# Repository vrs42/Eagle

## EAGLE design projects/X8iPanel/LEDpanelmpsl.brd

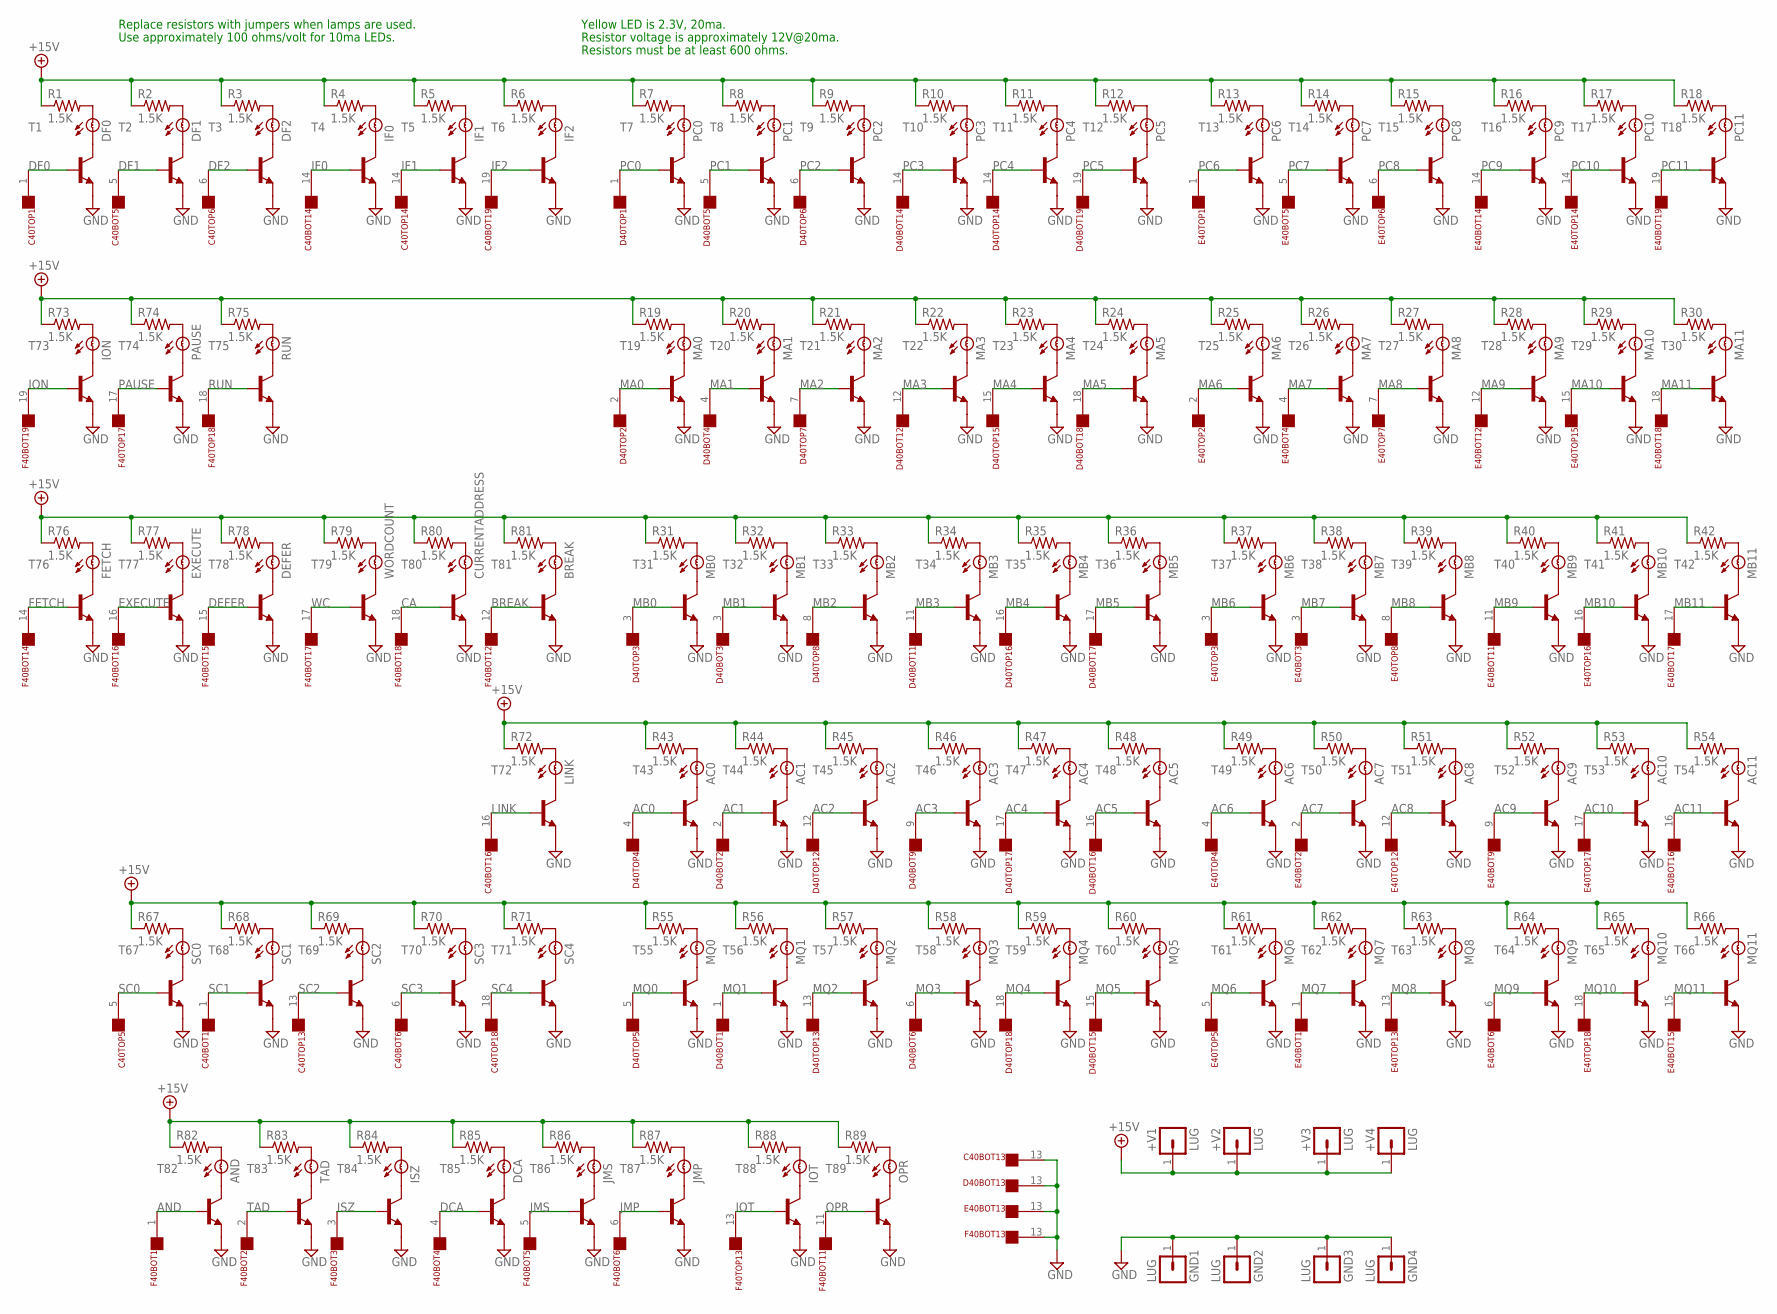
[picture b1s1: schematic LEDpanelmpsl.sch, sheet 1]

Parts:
+V1, +V2, +V3, +V4: LUG; SPADELUG
AC0, AC1, AC2, AC3, AC4, AC5, AC6, AC7, AC8, AC9, AC10, AC11: BULB
AND: BULB
BREAK: BULB
C40BOT, C40TOP: FLEX19
CURRENTADDRESS: BULB
D40BOT, D40TOP: FLEX19
DCA: BULB
DEFER: BULB
DF0, DF1, DF2: BULB
E40BOT, E40TOP: FLEX19
EXECUTE: BULB
F40BOT, F40TOP: FLEX19
FETCH: BULB
GND1, GND2, GND3, GND4: LUG; SPADELUG
IF0, IF1, IF2: BULB
ION: BULB
IOT: BULB
ISZ: BULB
JMP: BULB
JMS: BULB
LINK: BULB
MA0, MA1, MA2, MA3, MA4, MA5, MA6, MA7, MA8, MA9, MA10, MA11: BULB
MB0, MB1, MB2, MB3, MB4, MB5, MB6, MB7, MB8, MB9, MB10, MB11: BULB
MQ0, MQ1, MQ2, MQ3, MQ4, MQ5, MQ6, MQ7, MQ8, MQ9, MQ10, MQ11: BULB
OPR: BULB
PAUSE: BULB
PC0, PC1, PC2, PC3, PC4, PC5, PC6, PC7, PC8, PC9, PC10, PC11: BULB
R1, R2, R3, R4, R5, R6, R7, R8, R9, R10, R11, R12, R13, R14, R15, R16, R17, R18, R19, R20, R21, R22, R23, R24, R25, R26, R27, R28, R29, R30, R31, R32, R33, R34, R35, R36, R37, R38, R39, R40, R41, R42, R43, R44, R45, R46, R47, R48, R49, R50, R51, R52, R53, R54, R55, R56, R57, R58, R59, R60, R61, R62, R63, R64, R65, R66, R67, R68, R69, R70, R71, R72, R73, R74, R75, R76, R77, R78, R79, R80, R81, R82, R83, R84, R85, R86, R87, R88, R89: 1.5K; 0207/10
RUN: BULB
SC0, SC1, SC2, SC3, SC4: BULB
T1, T2, T3, T4, T5, T6, T7, T8, T9, T10, T11, T12, T13, T14, T15, T16, T17, T18, T19, T20, T21, T22, T23, T24, T25, T26, T27, T28, T29, T30, T31, T32, T33, T34, T35, T36, T37, T38, T39, T40, T41, T42, T43, T44, T45, T46, T47, T48, T49, T50, T51, T52, T53, T54, T55, T56, T57, T58, T59, T60, T61, T62, T63, T64, T65, T66, T67, T68, T69, T70, T71, T72, T73, T74, T75, T76, T77, T78, T79, T80, T81, T82, T83, T84, T85, T86, T87, T88, T89: MPS2222A-NPN-TO92-CBE; TO92-CBE
TAD: BULB
WORDCOUNT: BULB

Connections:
+15V: +V1.1, +V2.1, +V3.1, +V4.1, R1.1, R2.1, R3.1, R4.1, R5.1, R6.1, R7.1, R8.1, R9.1, R10.1, R11.1, R12.1, R13.1, R14.1, R15.1, R16.1, R17.1, R18.1, R19.1, R20.1, R21.1, R22.1, R23.1, R24.1, R25.1, R26.1, R27.1, R28.1, R29.1, R30.1, R31.1, R32.1, R33.1, R34.1, R35.1, R36.1, R37.1, R38.1, R39.1, R40.1, R41.1, R42.1, R43.1, R44.1, R45.1, R46.1, R47.1, R48.1, R49.1, R50.1, R51.1, R52.1, R53.1, R54.1, R55.1, R56.1, R57.1, R58.1, R59.1, R60.1, R61.1, R62.1, R63.1, R64.1, R65.1, R66.1, R67.1, R68.1, R69.1, R70.1, R71.1, R72.1, R73.1, R74.1, R75.1, R76.1, R77.1, R78.1, R79.1, R80.1, R81.1, R82.1, R83.1, R84.1, R85.1, R86.1, R87.1, R88.1, R89.1
AC0: D40TOP.4, T43.B; also elsewhere on the board
AC1: D40BOT.2, T44.B; also elsewhere on the board
AC2: D40TOP.12, T45.B; also elsewhere on the board
AC3: D40BOT.9, T46.B; also elsewhere on the board
AC4: D40TOP.17, T47.B; also elsewhere on the board
AC5: D40BOT.16, T48.B; also elsewhere on the board
AC6: E40TOP.4, T49.B; also elsewhere on the board
AC7: E40BOT.2, T50.B; also elsewhere on the board
AC8: E40TOP.12, T51.B; also elsewhere on the board
AC9: E40BOT.9, T52.B; also elsewhere on the board
AC10: E40TOP.17, T53.B; also elsewhere on the board
AC11: E40BOT.16, T54.B; also elsewhere on the board
AND: F40BOT.1, T82.B; also elsewhere on the board
BREAK: F40BOT.12, T81.B; also elsewhere on the board
CA: F40BOT.18, T80.B; also elsewhere on the board
DCA: F40BOT.4, T85.B; also elsewhere on the board
DEFER: F40BOT.15, T78.B; also elsewhere on the board
DF0: C40TOP.1, T1.B; also elsewhere on the board
DF1: C40BOT.5, T2.B; also elsewhere on the board
DF2: C40TOP.6, T3.B; also elsewhere on the board
EXECUTE: F40BOT.16, T77.B; also elsewhere on the board
FETCH: F40BOT.14, T76.B; also elsewhere on the board
GND: C40BOT.13, D40BOT.13, E40BOT.13, F40BOT.13, GND1.1, GND2.1, GND3.1, GND4.1, T1.E, T2.E, T3.E, T4.E, T5.E, T6.E, T7.E, T8.E, T9.E, T10.E, T11.E, T12.E, T13.E, T14.E, T15.E, T16.E, T17.E, T18.E, T19.E, T20.E, T21.E, T22.E, T23.E, T24.E, T25.E, T26.E, T27.E, T28.E, T29.E, T30.E, T31.E, T32.E, T33.E, T34.E, T35.E, T36.E, T37.E, T38.E, T39.E, T40.E, T41.E, T42.E, T43.E, T44.E, T45.E, T46.E, T47.E, T48.E, T49.E, T50.E, T51.E, T52.E, T53.E, T54.E, T55.E, T56.E, T57.E, T58.E, T59.E, T60.E, T61.E, T62.E, T63.E, T64.E, T65.E, T66.E, T67.E, T68.E, T69.E, T70.E, T71.E, T72.E, T73.E, T74.E, T75.E, T76.E, T77.E, T78.E, T79.E, T80.E, T81.E, T82.E, T83.E, T84.E, T85.E, T86.E, T87.E, T88.E, T89.E; also elsewhere on the board
IF0: C40BOT.14, T4.B; also elsewhere on the board
IF1: C40TOP.14, T5.B; also elsewhere on the board
IF2: C40BOT.19, T6.B; also elsewhere on the board
ION: F40BOT.19, T73.B; also elsewhere on the board
IOT: F40TOP.13, T88.B; also elsewhere on the board
ISZ: F40BOT.3, T84.B; also elsewhere on the board
JMP: F40BOT.6, T87.B; also elsewhere on the board
JMS: F40BOT.5, T86.B; also elsewhere on the board
LINK: C40BOT.16, T72.B; also elsewhere on the board
MA0: D40TOP.2, T19.B; also elsewhere on the board
MA1: D40BOT.4, T20.B; also elsewhere on the board
MA2: D40TOP.7, T21.B; also elsewhere on the board
MA3: D40BOT.12, T22.B; also elsewhere on the board
MA4: D40TOP.15, T23.B; also elsewhere on the board
MA5: D40BOT.18, T24.B; also elsewhere on the board
MA6: E40TOP.2, T25.B; also elsewhere on the board
MA7: E40BOT.4, T26.B; also elsewhere on the board
MA8: E40TOP.7, T27.B; also elsewhere on the board
MA9: E40BOT.12, T28.B; also elsewhere on the board
MA10: E40TOP.15, T29.B; also elsewhere on the board
MA11: E40BOT.18, T30.B; also elsewhere on the board
MB0: D40TOP.3, T31.B; also elsewhere on the board
MB1: D40BOT.3, T32.B; also elsewhere on the board
MB2: D40TOP.8, T33.B; also elsewhere on the board
MB3: D40BOT.11, T34.B; also elsewhere on the board
MB4: D40TOP.16, T35.B; also elsewhere on the board
MB5: D40BOT.17, T36.B; also elsewhere on the board
MB6: E40TOP.3, T37.B; also elsewhere on the board
MB7: E40BOT.3, T38.B; also elsewhere on the board
MB8: E40TOP.8, T39.B; also elsewhere on the board
MB9: E40BOT.11, T40.B; also elsewhere on the board
MB10: E40TOP.16, T41.B; also elsewhere on the board
MB11: E40BOT.17, T42.B; also elsewhere on the board
MQ0: D40TOP.5, T55.B; also elsewhere on the board
MQ1: D40BOT.1, T56.B; also elsewhere on the board
MQ2: D40TOP.13, T57.B; also elsewhere on the board
MQ3: D40BOT.6, T58.B; also elsewhere on the board
MQ4: D40TOP.18, T59.B; also elsewhere on the board
MQ5: D40BOT.15, T60.B; also elsewhere on the board
MQ6: E40TOP.5, T61.B; also elsewhere on the board
MQ7: E40BOT.1, T62.B; also elsewhere on the board
MQ8: E40TOP.13, T63.B; also elsewhere on the board
MQ9: E40BOT.6, T64.B; also elsewhere on the board
MQ10: E40TOP.18, T65.B; also elsewhere on the board
MQ11: E40BOT.15, T66.B; also elsewhere on the board
unnamed: DF0.B, T1.C
unnamed: DF1.B, T2.C
unnamed: DF2.B, T3.C
unnamed: IF0.B, T4.C
unnamed: IF1.B, T5.C
unnamed: IF2.B, T6.C
unnamed: PC0.B, T7.C
unnamed: PC1.B, T8.C
unnamed: PC2.B, T9.C
unnamed: PC3.B, T10.C
unnamed: PC4.B, T11.C
unnamed: PC5.B, T12.C
unnamed: PC6.B, T13.C
unnamed: PC7.B, T14.C
unnamed: PC8.B, T15.C
unnamed: PC9.B, T16.C
unnamed: PC10.B, T17.C
unnamed: PC11.B, T18.C
unnamed: MA0.B, T19.C
unnamed: MA1.B, T20.C
unnamed: MA2.B, T21.C
unnamed: MA3.B, T22.C
unnamed: MA4.B, T23.C
unnamed: MA5.B, T24.C
unnamed: MA6.B, T25.C
unnamed: MA7.B, T26.C
unnamed: MA8.B, T27.C
unnamed: MA9.B, T28.C
unnamed: MA10.B, T29.C
unnamed: MA11.B, T30.C
unnamed: MB0.B, T31.C
unnamed: MB1.B, T32.C
unnamed: MB2.B, T33.C
unnamed: MB3.B, T34.C
unnamed: MB4.B, T35.C
unnamed: MB5.B, T36.C
unnamed: MB6.B, T37.C
unnamed: MB7.B, T38.C
unnamed: MB8.B, T39.C
unnamed: MB9.B, T40.C
unnamed: MB10.B, T41.C
unnamed: MB11.B, T42.C
unnamed: AC0.B, T43.C
unnamed: AC1.B, T44.C
unnamed: AC2.B, T45.C
unnamed: AC3.B, T46.C
unnamed: AC4.B, T47.C
unnamed: AC5.B, T48.C
unnamed: AC6.B, T49.C
unnamed: AC7.B, T50.C
unnamed: AC8.B, T51.C
unnamed: AC9.B, T52.C
unnamed: AC10.B, T53.C
unnamed: AC11.B, T54.C
unnamed: MQ0.B, T55.C
unnamed: MQ1.B, T56.C
unnamed: MQ2.B, T57.C
unnamed: MQ3.B, T58.C
unnamed: MQ4.B, T59.C
unnamed: MQ5.B, T60.C
unnamed: MQ6.B, T61.C
unnamed: MQ7.B, T62.C
unnamed: MQ8.B, T63.C
unnamed: MQ9.B, T64.C
unnamed: MQ10.B, T65.C
unnamed: MQ11.B, T66.C
unnamed: SC0.B, T67.C
unnamed: SC1.B, T68.C
unnamed: SC2.B, T69.C
unnamed: SC3.B, T70.C
unnamed: SC4.B, T71.C
unnamed: LINK.B, T72.C
unnamed: ION.B, T73.C
unnamed: PAUSE.B, T74.C
unnamed: RUN.B, T75.C
unnamed: FETCH.B, T76.C
unnamed: EXECUTE.B, T77.C
unnamed: DEFER.B, T78.C
unnamed: T79.C, WORDCOUNT.B
unnamed: CURRENTADDRESS.B, T80.C
unnamed: BREAK.B, T81.C
unnamed: AND.B, T82.C
unnamed: T83.C, TAD.B
unnamed: ISZ.B, T84.C
unnamed: DCA.B, T85.C
unnamed: JMS.B, T86.C
unnamed: JMP.B, T87.C
unnamed: IOT.B, T88.C
unnamed: OPR.B, T89.C
unnamed: DF0.A, R1.2
unnamed: DF1.A, R2.2
unnamed: DF2.A, R3.2
unnamed: IF0.A, R4.2
unnamed: IF1.A, R5.2
unnamed: IF2.A, R6.2
unnamed: PC0.A, R7.2
unnamed: PC1.A, R8.2
unnamed: PC2.A, R9.2
unnamed: PC3.A, R10.2
unnamed: PC4.A, R11.2
unnamed: PC5.A, R12.2
unnamed: PC6.A, R13.2
unnamed: PC7.A, R14.2
unnamed: PC8.A, R15.2
unnamed: PC9.A, R16.2
unnamed: PC10.A, R17.2
unnamed: PC11.A, R18.2
unnamed: ION.A, R73.2
unnamed: PAUSE.A, R74.2
unnamed: R75.2, RUN.A
unnamed: MA0.A, R19.2
unnamed: MA1.A, R20.2
unnamed: MA2.A, R21.2
unnamed: MA3.A, R22.2
unnamed: MA4.A, R23.2
unnamed: MA5.A, R24.2
unnamed: MA6.A, R25.2
unnamed: MA7.A, R26.2
unnamed: MA8.A, R27.2
unnamed: MA9.A, R28.2
unnamed: MA10.A, R29.2
unnamed: MA11.A, R30.2
unnamed: FETCH.A, R76.2
unnamed: EXECUTE.A, R77.2
unnamed: DEFER.A, R78.2
unnamed: R79.2, WORDCOUNT.A
unnamed: CURRENTADDRESS.A, R80.2
unnamed: BREAK.A, R81.2
unnamed: LINK.A, R72.2
unnamed: MB0.A, R31.2
unnamed: MB1.A, R32.2
unnamed: MB2.A, R33.2
unnamed: MB3.A, R34.2
unnamed: MB4.A, R35.2
unnamed: MB5.A, R36.2
unnamed: MB6.A, R37.2
unnamed: MB7.A, R38.2
unnamed: MB8.A, R39.2
unnamed: MB9.A, R40.2
unnamed: MB10.A, R41.2
unnamed: MB11.A, R42.2
unnamed: AC0.A, R43.2
unnamed: AC1.A, R44.2
unnamed: AC2.A, R45.2
unnamed: AC3.A, R46.2
unnamed: AC4.A, R47.2
unnamed: AC5.A, R48.2
unnamed: AC6.A, R49.2
unnamed: AC7.A, R50.2
unnamed: AC8.A, R51.2
unnamed: AC9.A, R52.2
unnamed: AC10.A, R53.2
unnamed: AC11.A, R54.2
unnamed: R67.2, SC0.A
unnamed: R68.2, SC1.A
unnamed: R69.2, SC2.A
unnamed: R70.2, SC3.A
unnamed: R71.2, SC4.A
unnamed: MQ11.A, R66.2
unnamed: MQ10.A, R65.2
unnamed: MQ9.A, R64.2
unnamed: MQ8.A, R63.2
unnamed: MQ7.A, R62.2
unnamed: MQ6.A, R61.2
unnamed: MQ5.A, R60.2
unnamed: MQ4.A, R59.2
unnamed: MQ3.A, R58.2
unnamed: MQ2.A, R57.2
unnamed: MQ1.A, R56.2
unnamed: MQ0.A, R55.2
unnamed: AND.A, R82.2
unnamed: R83.2, TAD.A
unnamed: ISZ.A, R84.2
unnamed: DCA.A, R85.2
unnamed: JMS.A, R86.2
unnamed: JMP.A, R87.2
unnamed: IOT.A, R88.2
unnamed: OPR.A, R89.2
OPR: F40BOT.11, T89.B; also elsewhere on the board
PAUSE: F40TOP.17, T74.B; also elsewhere on the board
PC0: D40TOP.1, T7.B; also elsewhere on the board
PC1: D40BOT.5, T8.B; also elsewhere on the board
PC2: D40TOP.6, T9.B; also elsewhere on the board
PC3: D40BOT.14, T10.B; also elsewhere on the board
PC4: D40TOP.14, T11.B; also elsewhere on the board
PC5: D40BOT.19, T12.B; also elsewhere on the board
PC6: E40TOP.1, T13.B; also elsewhere on the board
PC7: E40BOT.5, T14.B; also elsewhere on the board
PC8: E40TOP.6, T15.B; also elsewhere on the board
PC9: E40BOT.14, T16.B; also elsewhere on the board
PC10: E40TOP.14, T17.B; also elsewhere on the board
PC11: E40BOT.19, T18.B; also elsewhere on the board
RUN: F40TOP.18, T75.B; also elsewhere on the board
SC0: C40TOP.5, T67.B; also elsewhere on the board
SC1: C40BOT.1, T68.B; also elsewhere on the board
SC2: C40TOP.13, T69.B; also elsewhere on the board
SC3: C40BOT.6, T70.B; also elsewhere on the board
SC4: C40TOP.18, T71.B; also elsewhere on the board
TAD: F40BOT.2, T83.B; also elsewhere on the board
WC: F40BOT.17, T79.B; also elsewhere on the board

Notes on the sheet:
Replace resistors with jumpers when lamps are used.
Use approximately 100 ohms/volt for 10ma LEDs.
Yellow LED is 2.3V, 20ma.
Resistor voltage is approximately 12V@20ma.
Resistors must be at least 600 ohms.

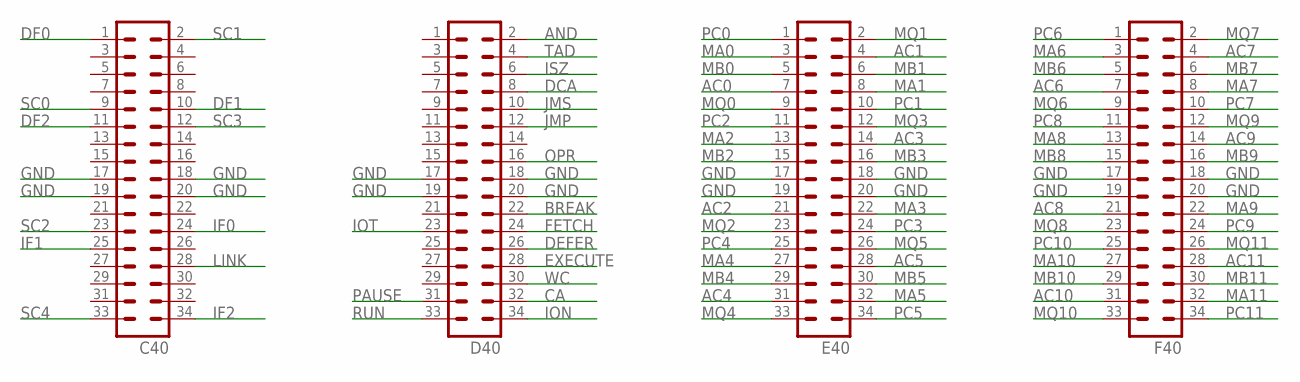
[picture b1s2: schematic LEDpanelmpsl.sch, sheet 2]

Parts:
C40: MA17-2
D40: MA17-2
E40: MA17-2
F40: MA17-2

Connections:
AC0: E40.7; also elsewhere on the board
AC1: E40.4; also elsewhere on the board
AC2: E40.21; also elsewhere on the board
AC3: E40.14; also elsewhere on the board
AC4: E40.31; also elsewhere on the board
AC5: E40.28; also elsewhere on the board
AC6: F40.7; also elsewhere on the board
AC7: F40.4; also elsewhere on the board
AC8: F40.21; also elsewhere on the board
AC9: F40.14; also elsewhere on the board
AC10: F40.31; also elsewhere on the board
AC11: F40.28; also elsewhere on the board
AND: D40.2; also elsewhere on the board
BREAK: D40.22; also elsewhere on the board
CA: D40.32; also elsewhere on the board
DCA: D40.8; also elsewhere on the board
DEFER: D40.26; also elsewhere on the board
DF0: C40.1; also elsewhere on the board
DF1: C40.10; also elsewhere on the board
DF2: C40.11; also elsewhere on the board
EXECUTE: D40.28; also elsewhere on the board
FETCH: D40.24; also elsewhere on the board
GND: C40.17, C40.18, C40.19, C40.20, D40.17, D40.18, D40.19, D40.20, E40.17, E40.18, E40.19, E40.20, F40.17, F40.18, F40.19, F40.20; also elsewhere on the board
IF0: C40.24; also elsewhere on the board
IF1: C40.25; also elsewhere on the board
IF2: C40.34; also elsewhere on the board
ION: D40.34; also elsewhere on the board
IOT: D40.23; also elsewhere on the board
ISZ: D40.6; also elsewhere on the board
JMP: D40.12; also elsewhere on the board
JMS: D40.10; also elsewhere on the board
LINK: C40.28; also elsewhere on the board
MA0: E40.3; also elsewhere on the board
MA1: E40.8; also elsewhere on the board
MA2: E40.13; also elsewhere on the board
MA3: E40.22; also elsewhere on the board
MA4: E40.27; also elsewhere on the board
MA5: E40.32; also elsewhere on the board
MA6: F40.3; also elsewhere on the board
MA7: F40.8; also elsewhere on the board
MA8: F40.13; also elsewhere on the board
MA9: F40.22; also elsewhere on the board
MA10: F40.27; also elsewhere on the board
MA11: F40.32; also elsewhere on the board
MB0: E40.5; also elsewhere on the board
MB1: E40.6; also elsewhere on the board
MB2: E40.15; also elsewhere on the board
MB3: E40.16; also elsewhere on the board
MB4: E40.29; also elsewhere on the board
MB5: E40.30; also elsewhere on the board
MB6: F40.5; also elsewhere on the board
MB7: F40.6; also elsewhere on the board
MB8: F40.15; also elsewhere on the board
MB9: F40.16; also elsewhere on the board
MB10: F40.29; also elsewhere on the board
MB11: F40.30; also elsewhere on the board
MQ0: E40.9; also elsewhere on the board
MQ1: E40.2; also elsewhere on the board
MQ2: E40.23; also elsewhere on the board
MQ3: E40.12; also elsewhere on the board
MQ4: E40.33; also elsewhere on the board
MQ5: E40.26; also elsewhere on the board
MQ6: F40.9; also elsewhere on the board
MQ7: F40.2; also elsewhere on the board
MQ8: F40.23; also elsewhere on the board
MQ9: F40.12; also elsewhere on the board
MQ10: F40.33; also elsewhere on the board
MQ11: F40.26; also elsewhere on the board
OPR: D40.16; also elsewhere on the board
PAUSE: D40.31; also elsewhere on the board
PC0: E40.1; also elsewhere on the board
PC1: E40.10; also elsewhere on the board
PC2: E40.11; also elsewhere on the board
PC3: E40.24; also elsewhere on the board
PC4: E40.25; also elsewhere on the board
PC5: E40.34; also elsewhere on the board
PC6: F40.1; also elsewhere on the board
PC7: F40.10; also elsewhere on the board
PC8: F40.11; also elsewhere on the board
PC9: F40.24; also elsewhere on the board
PC10: F40.25; also elsewhere on the board
PC11: F40.34; also elsewhere on the board
RUN: D40.33; also elsewhere on the board
SC0: C40.9; also elsewhere on the board
SC1: C40.2; also elsewhere on the board
SC2: C40.23; also elsewhere on the board
SC3: C40.12; also elsewhere on the board
SC4: C40.33; also elsewhere on the board
TAD: D40.4; also elsewhere on the board
WC: D40.30; also elsewhere on the board

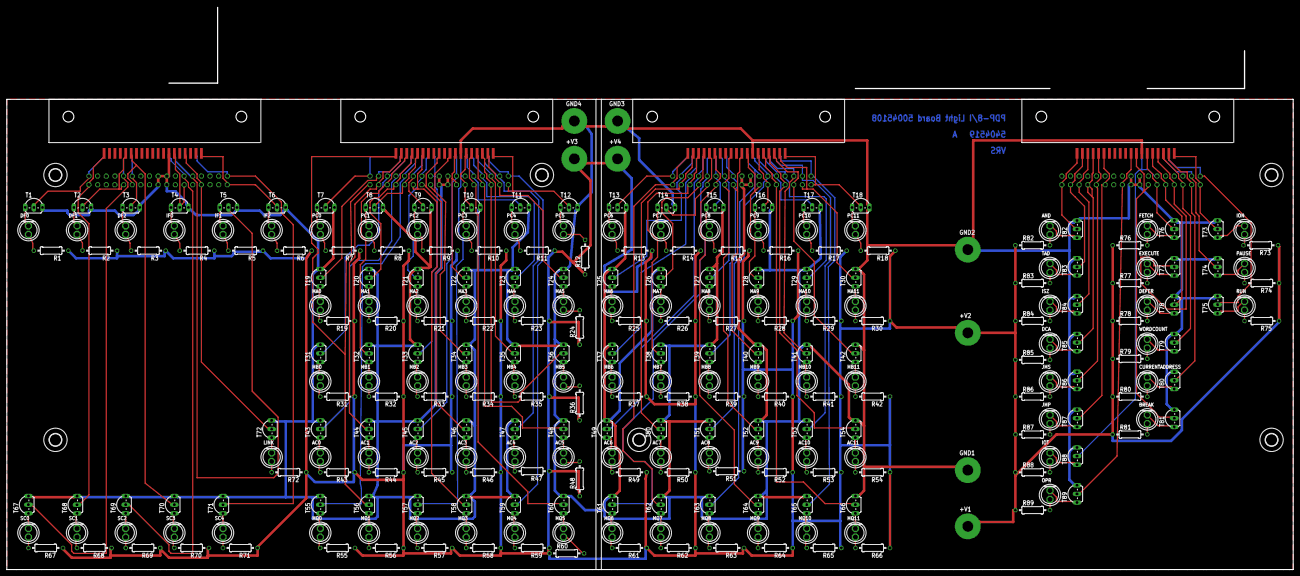
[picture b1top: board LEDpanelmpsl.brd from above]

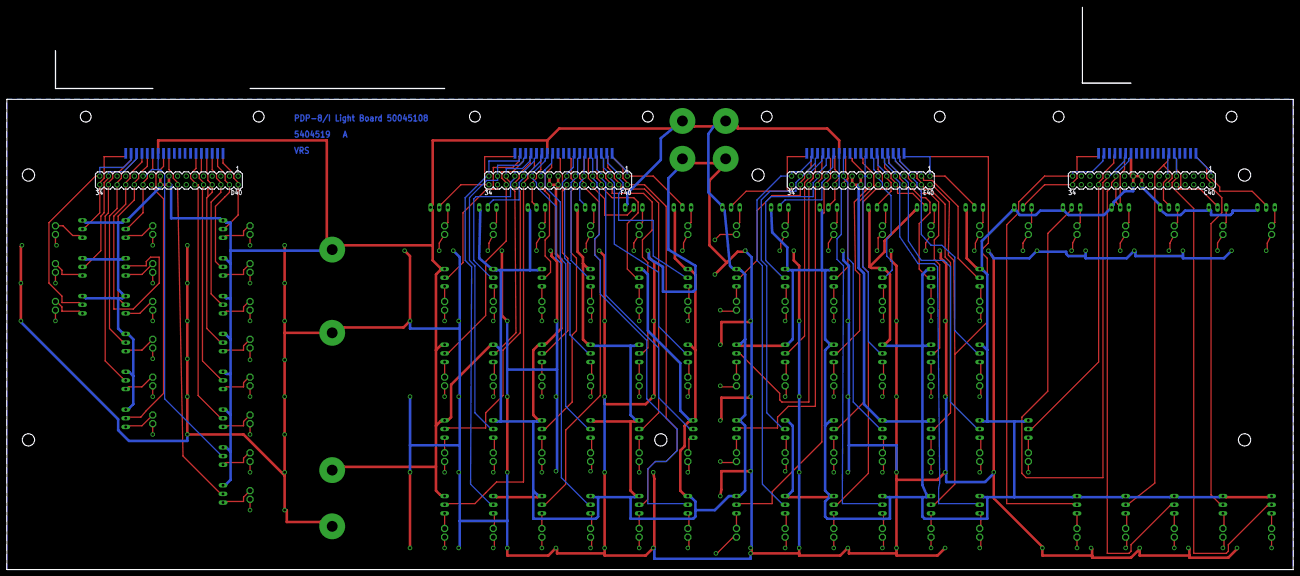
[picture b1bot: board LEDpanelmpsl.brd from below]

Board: 2 copper layers, 377.8 x 138.1 mm, 297 parts (8 on the bottom side), 269 nets.

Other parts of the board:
U$1, U$2, U$3, U$4: STRAIN-RELIEF
U$5, U$6, U$7, U$8, U$9, U$11: 3,6

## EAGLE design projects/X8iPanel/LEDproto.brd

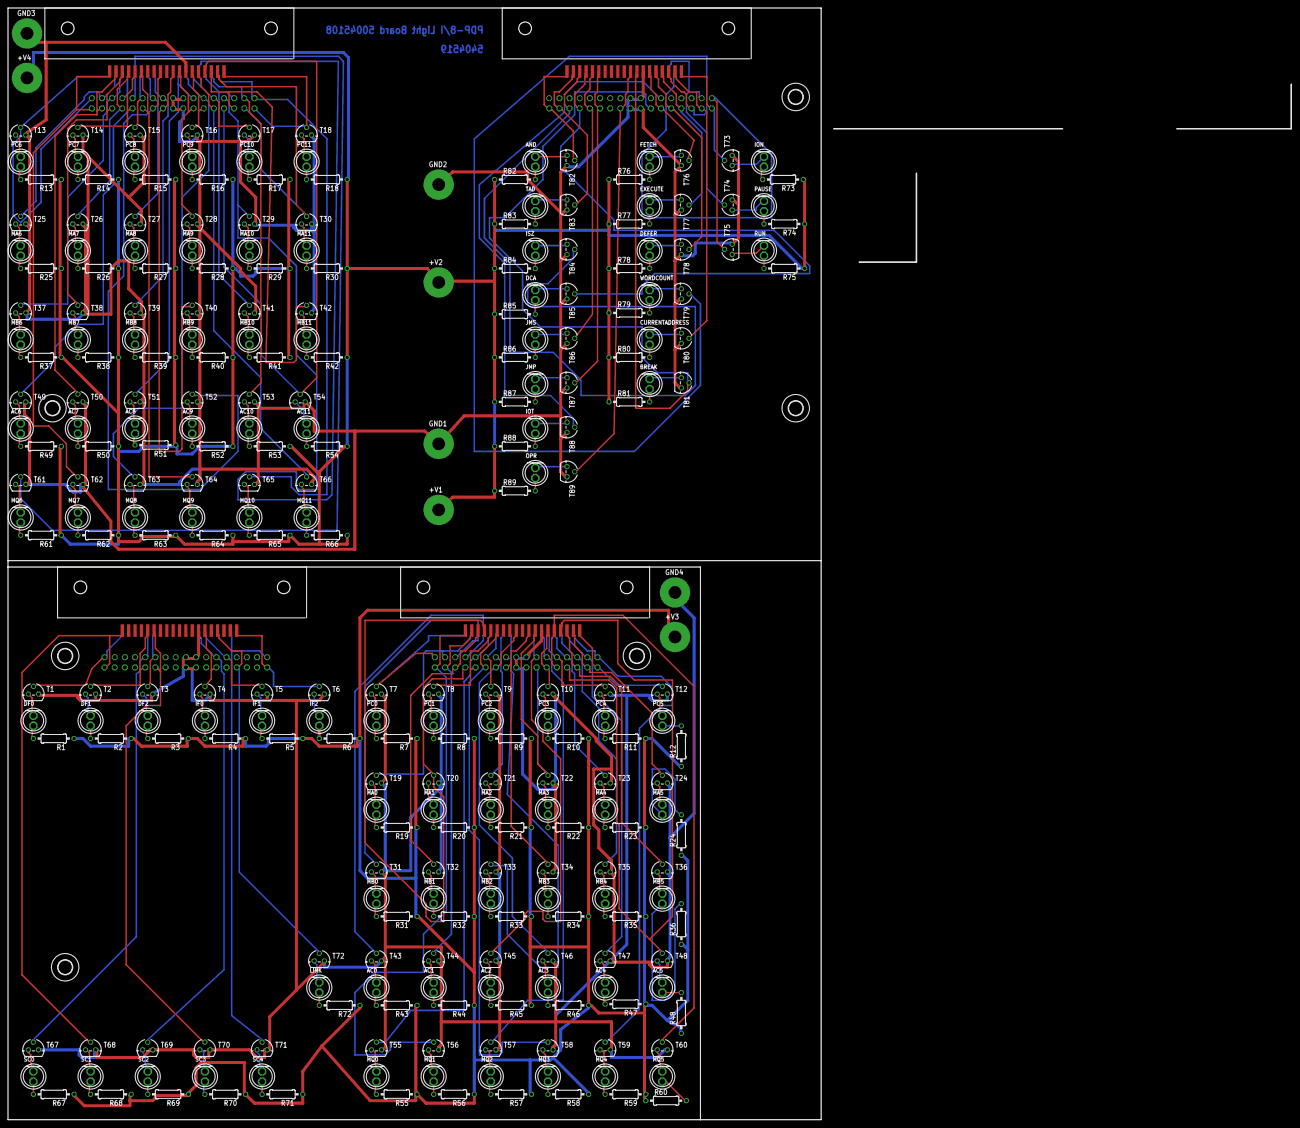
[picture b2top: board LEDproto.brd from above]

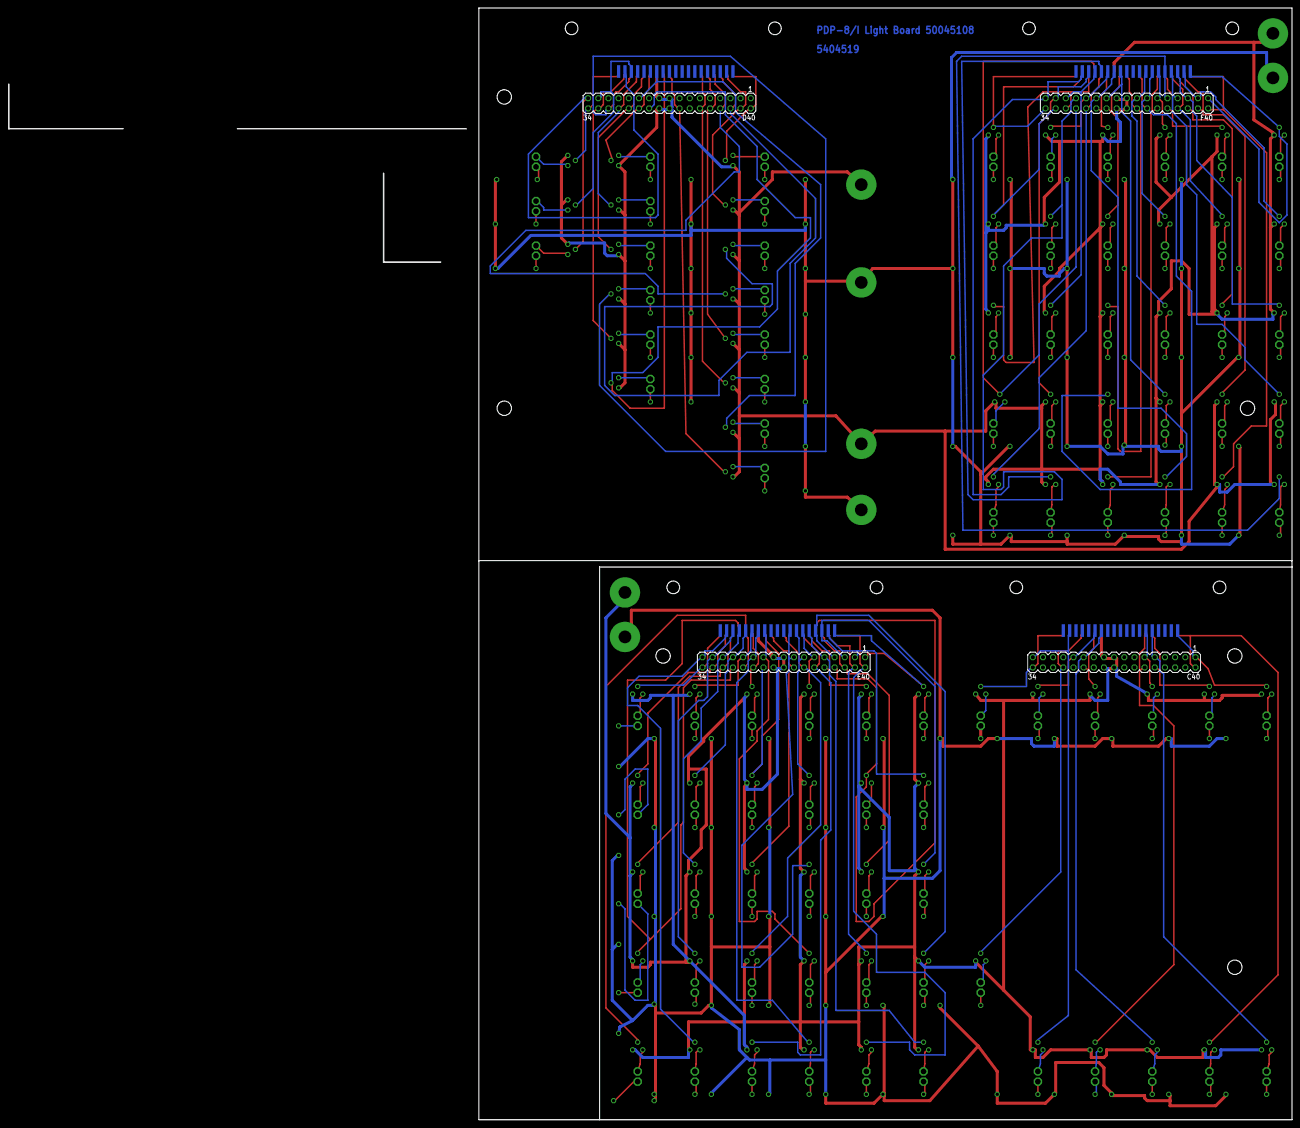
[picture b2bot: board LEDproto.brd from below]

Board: 2 copper layers, 203.2 x 277.8 mm, 297 parts (8 on the bottom side), 269 nets.

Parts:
+V1, +V2, +V3, +V4: LUG; SPADELUG
AC0, AC1, AC2, AC3, AC4, AC5, AC6, AC7, AC8, AC9, AC10, AC11: BULB
AND: BULB
BREAK: BULB
C40: MA17-2
C40BOT, C40TOP: FLEX19
CURRENTADDRESS: BULB
D40: MA17-2
D40BOT, D40TOP: FLEX19
DCA: BULB
DEFER: BULB
DF0, DF1, DF2: BULB
E40: MA17-2
E40BOT, E40TOP: FLEX19
EXECUTE: BULB
F40: MA17-2
F40BOT, F40TOP: FLEX19
FETCH: BULB
GND1, GND2, GND3, GND4: LUG; SPADELUG
IF0, IF1, IF2: BULB
ION: BULB
IOT: BULB
ISZ: BULB
JMP: BULB
JMS: BULB
LINK: BULB
MA0, MA1, MA2, MA3, MA4, MA5, MA6, MA7, MA8, MA9, MA10, MA11: BULB
MB0, MB1, MB2, MB3, MB4, MB5, MB6, MB7, MB8, MB9, MB10, MB11: BULB
MQ0, MQ1, MQ2, MQ3, MQ4, MQ5, MQ6, MQ7, MQ8, MQ9, MQ10, MQ11: BULB
OPR: BULB
PAUSE: BULB
PC0, PC1, PC2, PC3, PC4, PC5, PC6, PC7, PC8, PC9, PC10, PC11: BULB
R1, R2, R3, R4, R5, R6, R7, R8, R9, R10, R11, R12, R13, R14, R15, R16, R17, R18, R19, R20, R21, R22, R23, R24, R25, R26, R27, R28, R29, R30, R31, R32, R33, R34, R35, R36, R37, R38, R39, R40, R41, R42, R43, R44, R45, R46, R47, R48, R49, R50, R51, R52, R53, R54, R55, R56, R57, R58, R59, R60, R61, R62, R63, R64, R65, R66, R67, R68, R69, R70, R71, R72, R73, R74, R75, R76, R77, R78, R79, R80, R81, R82, R83, R84, R85, R86, R87, R88, R89: 1.5K; 0207/10
RUN: BULB
SC0, SC1, SC2, SC3, SC4: BULB
T1, T2, T3, T4, T5, T6, T7, T8, T9, T10, T11, T12, T13, T14, T15, T16, T17, T18, T19, T20, T21, T22, T23, T24, T25, T26, T27, T28, T29, T30, T31, T32, T33, T34, T35, T36, T37, T38, T39, T40, T41, T42, T43, T44, T45, T46, T47, T48, T49, T50, T51, T52, T53, T54, T55, T56, T57, T58, T59, T60, T61, T62, T63, T64, T65, T66, T67, T68, T69, T70, T71, T72, T73, T74, T75, T76, T77, T78, T79, T80, T81, T82, T83, T84, T85, T86, T87, T88, T89: 2N2222; TO92
TAD: BULB
U$1, U$2, U$3, U$4: STRAIN-RELIEF
U$5, U$6, U$7, U$8, U$9, U$11: 3,6
WORDCOUNT: BULB

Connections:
+15V: +V1.1, +V2.1, +V3.1, +V4.1, R1.1, R2.1, R3.1, R4.1, R5.1, R6.1, R7.1, R8.1, R9.1, R10.1, R11.1, R12.1, R13.1, R14.1, R15.1, R16.1, R17.1, R18.1, R19.1, R20.1, R21.1, R22.1, R23.1, R24.1, R25.1, R26.1, R27.1, R28.1, R29.1, R30.1, R31.1, R32.1, R33.1, R34.1, R35.1, R36.1, R37.1, R38.1, R39.1, R40.1, R41.1, R42.1, R43.1, R44.1, R45.1, R46.1, R47.1, R48.1, R49.1, R50.1, R51.1, R52.1, R53.1, R54.1, R55.1, R56.1, R57.1, R58.1, R59.1, R60.1, R61.1, R62.1, R63.1, R64.1, R65.1, R66.1, R67.1, R68.1, R69.1, R70.1, R71.1, R72.1, R73.1, R74.1, R75.1, R76.1, R77.1, R78.1, R79.1, R80.1, R81.1, R82.1, R83.1, R84.1, R85.1, R86.1, R87.1, R88.1, R89.1
AC0: D40TOP.4, E40.7, T43.2
AC1: D40BOT.2, E40.4, T44.2
AC2: D40TOP.12, E40.21, T45.2
AC3: D40BOT.9, E40.14, T46.2
AC4: D40TOP.17, E40.31, T47.2
AC5: D40BOT.16, E40.28, T48.2
AC6: E40TOP.4, F40.7, T49.2
AC7: E40BOT.2, F40.4, T50.2
AC8: E40TOP.12, F40.21, T51.2
AC9: E40BOT.9, F40.14, T52.2
AC10: E40TOP.17, F40.31, T53.2
AC11: E40BOT.16, F40.28, T54.2
AND: D40.2, F40BOT.1, T82.2
BREAK: D40.22, F40BOT.12, T81.2
CA: D40.32, F40BOT.18, T80.2
DCA: D40.8, F40BOT.4, T85.2
DEFER: D40.26, F40BOT.15, T78.2
DF0: C40.1, C40TOP.1, T1.2
DF1: C40.10, C40BOT.5, T2.2
DF2: C40.11, C40TOP.6, T3.2
EXECUTE: D40.28, F40BOT.16, T77.2
FETCH: D40.24, F40BOT.14, T76.2
GND: C40.17, C40.18, C40.19, C40.20, C40BOT.13, D40.17, D40.18, D40.19, D40.20, D40BOT.13, E40.17, E40.18, E40.19, E40.20, E40BOT.13, F40.17, F40.18, F40.19, F40.20, F40BOT.13, GND1.1, GND2.1, GND3.1, GND4.1, T1.1, T2.1, T3.1, T4.1, T5.1, T6.1, T7.1, T8.1, T9.1, T10.1, T11.1, T12.1, T13.1, T14.1, T15.1, T16.1, T17.1, T18.1, T19.1, T20.1, T21.1, T22.1, T23.1, T24.1, T25.1, T26.1, T27.1, T28.1, T29.1, T30.1, T31.1, T32.1, T33.1, T34.1, T35.1, T36.1, T37.1, T38.1, T39.1, T40.1, T41.1, T42.1, T43.1, T44.1, T45.1, T46.1, T47.1, T48.1, T49.1, T50.1, T51.1, T52.1, T53.1, T54.1, T55.1, T56.1, T57.1, T58.1, T59.1, T60.1, T61.1, T62.1, T63.1, T64.1, T65.1, T66.1, T67.1, T68.1, T69.1, T70.1, T71.1, T72.1, T73.1, T74.1, T75.1, T76.1, T77.1, T78.1, T79.1, T80.1, T81.1, T82.1, T83.1, T84.1, T85.1, T86.1, T87.1, T88.1, T89.1
IF0: C40.24, C40BOT.14, T4.2
IF1: C40.25, C40TOP.14, T5.2
IF2: C40.34, C40BOT.19, T6.2
ION: D40.34, F40BOT.19, T73.2
IOT: D40.23, F40TOP.13, T88.2
ISZ: D40.6, F40BOT.3, T84.2
JMP: D40.12, F40BOT.6, T87.2
JMS: D40.10, F40BOT.5, T86.2
LINK: C40.28, C40BOT.16, T72.2
MA0: D40TOP.2, E40.3, T19.2
MA1: D40BOT.4, E40.8, T20.2
MA2: D40TOP.7, E40.13, T21.2
MA3: D40BOT.12, E40.22, T22.2
MA4: D40TOP.15, E40.27, T23.2
MA5: D40BOT.18, E40.32, T24.2
MA6: E40TOP.2, F40.3, T25.2
MA7: E40BOT.4, F40.8, T26.2
MA8: E40TOP.7, F40.13, T27.2
MA9: E40BOT.12, F40.22, T28.2
MA10: E40TOP.15, F40.27, T29.2
MA11: E40BOT.18, F40.32, T30.2
MB0: D40TOP.3, E40.5, T31.2
MB1: D40BOT.3, E40.6, T32.2
MB2: D40TOP.8, E40.15, T33.2
MB3: D40BOT.11, E40.16, T34.2
MB4: D40TOP.16, E40.29, T35.2
MB5: D40BOT.17, E40.30, T36.2
MB6: E40TOP.3, F40.5, T37.2
MB7: E40BOT.3, F40.6, T38.2
MB8: E40TOP.8, F40.15, T39.2
MB9: E40BOT.11, F40.16, T40.2
MB10: E40TOP.16, F40.29, T41.2
MB11: E40BOT.17, F40.30, T42.2
MQ0: D40TOP.5, E40.9, T55.2
MQ1: D40BOT.1, E40.2, T56.2
MQ2: D40TOP.13, E40.23, T57.2
MQ3: D40BOT.6, E40.12, T58.2
MQ4: D40TOP.18, E40.33, T59.2
MQ5: D40BOT.15, E40.26, T60.2
MQ6: E40TOP.5, F40.9, T61.2
MQ7: E40BOT.1, F40.2, T62.2
MQ8: E40TOP.13, F40.23, T63.2
MQ9: E40BOT.6, F40.12, T64.2
MQ10: E40TOP.18, F40.33, T65.2
MQ11: E40BOT.15, F40.26, T66.2
unnamed: DF0.B, T1.3
unnamed: DF1.B, T2.3
unnamed: DF2.B, T3.3
unnamed: IF0.B, T4.3
unnamed: IF1.B, T5.3
unnamed: IF2.B, T6.3
unnamed: PC0.B, T7.3
unnamed: PC1.B, T8.3
unnamed: PC2.B, T9.3
unnamed: PC3.B, T10.3
unnamed: PC4.B, T11.3
unnamed: PC5.B, T12.3
unnamed: PC6.B, T13.3
unnamed: PC7.B, T14.3
unnamed: PC8.B, T15.3
unnamed: PC9.B, T16.3
unnamed: PC10.B, T17.3
unnamed: PC11.B, T18.3
unnamed: MA0.B, T19.3
unnamed: MA1.B, T20.3
unnamed: MA2.B, T21.3
unnamed: MA3.B, T22.3
unnamed: MA4.B, T23.3
unnamed: MA5.B, T24.3
unnamed: MA6.B, T25.3
unnamed: MA7.B, T26.3
unnamed: MA8.B, T27.3
unnamed: MA9.B, T28.3
unnamed: MA10.B, T29.3
unnamed: MA11.B, T30.3
unnamed: MB0.B, T31.3
unnamed: MB1.B, T32.3
unnamed: MB2.B, T33.3
unnamed: MB3.B, T34.3
unnamed: MB4.B, T35.3
unnamed: MB5.B, T36.3
unnamed: MB6.B, T37.3
unnamed: MB7.B, T38.3
unnamed: MB8.B, T39.3
unnamed: MB9.B, T40.3
unnamed: MB10.B, T41.3
unnamed: MB11.B, T42.3
unnamed: AC0.B, T43.3
unnamed: AC1.B, T44.3
unnamed: AC2.B, T45.3
unnamed: AC3.B, T46.3
unnamed: AC4.B, T47.3
unnamed: AC5.B, T48.3
unnamed: AC6.B, T49.3
unnamed: AC7.B, T50.3
unnamed: AC8.B, T51.3
unnamed: AC9.B, T52.3
unnamed: AC10.B, T53.3
unnamed: AC11.B, T54.3
unnamed: MQ0.B, T55.3
unnamed: MQ1.B, T56.3
unnamed: MQ2.B, T57.3
unnamed: MQ3.B, T58.3
unnamed: MQ4.B, T59.3
unnamed: MQ5.B, T60.3
unnamed: MQ6.B, T61.3
unnamed: MQ7.B, T62.3
unnamed: MQ8.B, T63.3
unnamed: MQ9.B, T64.3
unnamed: MQ10.B, T65.3
unnamed: MQ11.B, T66.3
unnamed: SC0.B, T67.3
unnamed: SC1.B, T68.3
unnamed: SC2.B, T69.3
unnamed: SC3.B, T70.3
unnamed: SC4.B, T71.3
unnamed: LINK.B, T72.3
unnamed: ION.B, T73.3
unnamed: PAUSE.B, T74.3
unnamed: RUN.B, T75.3
unnamed: FETCH.B, T76.3
unnamed: EXECUTE.B, T77.3
unnamed: DEFER.B, T78.3
unnamed: T79.3, WORDCOUNT.B
unnamed: CURRENTADDRESS.B, T80.3
unnamed: BREAK.B, T81.3
unnamed: AND.B, T82.3
unnamed: T83.3, TAD.B
unnamed: ISZ.B, T84.3
unnamed: DCA.B, T85.3
unnamed: JMS.B, T86.3
unnamed: JMP.B, T87.3
unnamed: IOT.B, T88.3
unnamed: OPR.B, T89.3
unnamed: DF0.A, R1.2
unnamed: DF1.A, R2.2
unnamed: DF2.A, R3.2
unnamed: IF0.A, R4.2
unnamed: IF1.A, R5.2
unnamed: IF2.A, R6.2
unnamed: PC0.A, R7.2
unnamed: PC1.A, R8.2
unnamed: PC2.A, R9.2
unnamed: PC3.A, R10.2
unnamed: PC4.A, R11.2
unnamed: PC5.A, R12.2
unnamed: PC6.A, R13.2
unnamed: PC7.A, R14.2
unnamed: PC8.A, R15.2
unnamed: PC9.A, R16.2
unnamed: PC10.A, R17.2
unnamed: PC11.A, R18.2
unnamed: ION.A, R73.2
unnamed: PAUSE.A, R74.2
unnamed: R75.2, RUN.A
unnamed: MA0.A, R19.2
unnamed: MA1.A, R20.2
unnamed: MA2.A, R21.2
unnamed: MA3.A, R22.2
unnamed: MA4.A, R23.2
unnamed: MA5.A, R24.2
unnamed: MA6.A, R25.2
unnamed: MA7.A, R26.2
unnamed: MA8.A, R27.2
unnamed: MA9.A, R28.2
unnamed: MA10.A, R29.2
unnamed: MA11.A, R30.2
unnamed: FETCH.A, R76.2
unnamed: EXECUTE.A, R77.2
unnamed: DEFER.A, R78.2
unnamed: R79.2, WORDCOUNT.A
unnamed: CURRENTADDRESS.A, R80.2
unnamed: BREAK.A, R81.2
unnamed: LINK.A, R72.2
unnamed: MB0.A, R31.2
unnamed: MB1.A, R32.2
unnamed: MB2.A, R33.2
unnamed: MB3.A, R34.2
unnamed: MB4.A, R35.2
unnamed: MB5.A, R36.2
unnamed: MB6.A, R37.2
unnamed: MB7.A, R38.2
unnamed: MB8.A, R39.2
unnamed: MB9.A, R40.2
unnamed: MB10.A, R41.2
unnamed: MB11.A, R42.2
unnamed: AC0.A, R43.2
unnamed: AC1.A, R44.2
unnamed: AC2.A, R45.2
unnamed: AC3.A, R46.2
unnamed: AC4.A, R47.2
unnamed: AC5.A, R48.2
unnamed: AC6.A, R49.2
unnamed: AC7.A, R50.2
unnamed: AC8.A, R51.2
unnamed: AC9.A, R52.2
unnamed: AC10.A, R53.2
unnamed: AC11.A, R54.2
unnamed: R67.2, SC0.A
unnamed: R68.2, SC1.A
unnamed: R69.2, SC2.A
unnamed: R70.2, SC3.A
unnamed: R71.2, SC4.A
unnamed: MQ11.A, R66.2
unnamed: MQ10.A, R65.2
unnamed: MQ9.A, R64.2
unnamed: MQ8.A, R63.2
unnamed: MQ7.A, R62.2
unnamed: MQ6.A, R61.2
unnamed: MQ5.A, R60.2
unnamed: MQ4.A, R59.2
unnamed: MQ3.A, R58.2
unnamed: MQ2.A, R57.2
unnamed: MQ1.A, R56.2
unnamed: MQ0.A, R55.2
unnamed: AND.A, R82.2
unnamed: R83.2, TAD.A
unnamed: ISZ.A, R84.2
unnamed: DCA.A, R85.2
unnamed: JMS.A, R86.2
unnamed: JMP.A, R87.2
unnamed: IOT.A, R88.2
unnamed: OPR.A, R89.2
OPR: D40.16, F40BOT.11, T89.2
PAUSE: D40.31, F40TOP.17, T74.2
PC0: D40TOP.1, E40.1, T7.2
PC1: D40BOT.5, E40.10, T8.2
PC2: D40TOP.6, E40.11, T9.2
PC3: D40BOT.14, E40.24, T10.2
PC4: D40TOP.14, E40.25, T11.2
PC5: D40BOT.19, E40.34, T12.2
PC6: E40TOP.1, F40.1, T13.2
PC7: E40BOT.5, F40.10, T14.2
PC8: E40TOP.6, F40.11, T15.2
PC9: E40BOT.14, F40.24, T16.2
PC10: E40TOP.14, F40.25, T17.2
PC11: E40BOT.19, F40.34, T18.2
RUN: D40.33, F40TOP.18, T75.2
SC0: C40.9, C40TOP.5, T67.2
SC1: C40.2, C40BOT.1, T68.2
SC2: C40.23, C40TOP.13, T69.2
SC3: C40.12, C40BOT.6, T70.2
SC4: C40.33, C40TOP.18, T71.2
TAD: D40.4, F40BOT.2, T83.2
WC: D40.30, F40BOT.17, T79.2
